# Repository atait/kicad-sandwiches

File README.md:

# KiSandwich
# KiSandwich

A KiCad plugin for designing **sandwich PCBs** — multiple boards bonded
together face-to-face into one device. Doing this lets you hide components
completely inside the stack, get 4-layer routing out of a pair of 2-layer
boards, and build truly zero-profile hardware (business cards, wallet-thin
gadgets, embedded speakers and microSD slots).

This construction technique is new and rarely used, so no design tools exist
for it — professional or otherwise. KiSandwich is an attempt to fill that gap:
you design one combined board in KiCad, and the plugin splits it into the
individual 2-layer boards you actually fabricate and bond.

## Concept

## Why would you do this

1. **Zero-profile design.** Build truly flat hardware — slip it in a wallet, embed it in a case, or hide it completely.
2. **Hide your components.** Recess and even hide parts into the board for things like backlit capacitive buttons.
3. **Get more routing layers.** Effectively get 4-layer routing out of a pair of 2-layer boards (or 6-layer out of three).
4. **Populate both sides cheaply.** Put components on both faces even if your pick-and-place only does one side.

This builds on [Oreo construction](https://hackaday.com/2019/01/18/oreo-construction-hiding-your-components-inside-the-pcb/),
which has more reasoning and a build example.
## Installation
### Install kigadgets
This is a wrapper for KiCAD's python SWIG. It is needed for version-independent action plugins. Follow instructions at [kigadgets](https://github.com/atait/kicad-python).

### Install kicad-sandwich action plugin
Clone this repository. Symlink the whole thing (`kicad-sandwiches`) into your kicad user plugins directory. This directory is located in ${KICAD_USER_DIR}/scripting/plugins, where ${KICAD_USER_DIR} depends on your operating system. You can find out where it is using the menu item "Tools > External Plugins > Reveal Plugin Folder". On macOS, you can avoid the terminal by right clicking the repo, making an "alias", and moving that alias to the plugins directory.

The next time you start pcbnew, you should see these icons in the menu bar.

If not, try going to Preferences>"action plugins" to search for them in the list and check the enable boxes.

## Examples
### Example files
The "examples" directory walks through a full design flow. The main design file is called "sandwich-example.kicad_pcb". It is designed as a 4-layer board with surface mount components on front and back. The image "pcbnew-snapshot.png" shows what the program *thinks* you are designing.

and here is what you are actually designing. Bottom board is green. Top board is red and transparent, and both ICs are recessed:

### Example footprints (tested and fabricated)
KiCAD footprints are found in kicad-sandwiches.pretty. Put them in a project library or a global library, and add that to your footprint paths to use them.

#### 2-board Arduino Nano
It is not quite zero profile because of the USBmicro but very close.

#### 3-board Arduino Nano
This is a 3-board sandwich with the Arduino Nano in the middle. It is completely hidden and zero profile. There is a hole so the reset button can be accessed.

#### Sandwich speaker
A zero-profile high-quality magnetic speaker (not a buzzer). It is almost exactly 5.2mm thick, so it fits with a 2mm midboard and 1.6mm outer boards. There is no room for screws, so it is glued in. Wire contacts are soldered to the midboard, so they are zero-profile too.

Tested with Digikey part: CLS0281MAE-L152

#### Hidden microSD card slot
A microSD card slot that is completely hidden and zero profile. It is accessed from the side of the sandwich.

## Designing
#### Actual layer meanings
The real thing will be stacked in the opposite order. F.Cu and B.Cu are used to represent the layers on the inside of the sandwich, while In1.Cu and In2.Cu represent what will become the outside of the sandwich. F and B will bond to one another with solder.

The reason for doing this is that blind vias make sense (except blind vias between In1 and In2). Components can be placed on F and B, but not In1 and In2. Most of the same DRC still applies, for example, a trace on F.Cu can pass over a buried via between B and In2.

**User.Eco1** makes cuts in the TOP board. Make sure cuts defined by Eco1 do not intersect footprints on Back. If it is a 2-board internal stack, put Eco1 openings around footprints on Front.

**User.Eco2** makes cuts in the LOW board. Make sure cuts defined by Eco2 do not intersect footprints on Front. If it is a 2-board internal stack, put Eco2 openings around footprints on Back.

**Margin *or* User.3** make cuts in the MID board if there is a 3-board stackup (i.e. 6 copper layers). In a 3-board stack, make sure there are slots in this layer for all footprints on front or back.

#### Running the scripts
Using the kisandwich plugin, this "board" is converted to two other files corresponding to the actual 2-layer boards: "kisandwich-out/sandwich-example-sandwich_\[LOW|TOP\].kicad_pcb". The plugin is activated with the  button, which gives a dialog with various options.

There are also entry points available to external python environments. These work on board files instead of the GUI's board.

#### Bonding pads
If you want a standard through via on one of your resulting boards, make this a *buried* via in the base design. A buried via between F.Cu/In1.Cu will get converted to a regular via on the LOW board. Buried vias between In1.Cu and In2.Cu make no sense! Those correspond to layers on the outside of the stackup.

kisandwich will interpret through vias as bonding points. It will tent them (covered by solder mask) on the outer sides, and de-tent them on the insides so that a big copper pad is exposed. When you get the PCBs, you put solder paste on these pads and reflow. Having a hole is extremely useful so you can stick in a soldering iron in case your reflow doesn't yield 100%.

Recommended bond pad parameters: Via diameter = 2 mm; Via hole = 1 mm

#### FreeCAD integration
In the same directory, all the boards are exported to VRML (.wrl) models.

**Todo: is this automated yet? KiCad 7 changed some VRML entry points**

**Todo: describe FreeCAD plugin installation here**

The models are assembled together in FreeCAD in the file "FreeCAD-out/stack-3dModel.FCStd". In FreeCAD, the lower board is translated down by one board thickness, and their appearances can be altered. Finally, a snapshot of the FreeCAD assembly is included in "FreeCAD-out/assembled-snapshot.png".

#### DRC
Both the source combined design and kisandwich outputs should roughly make sense as PCBs. The whole process of kisandwiches is designed to make both perspectives sensible.
The outputs must be valid 2-layer PCBs. The combined design should be a valid 6-layer or 4-layer PCB design, just with some new features and some other features verboten. This means DRC is a valid and highly useful tool.

The overall design should pass DRC, except for board outline violations. This will catch things like wires too close, and it won't hit non-errors like F.Cu crossing a B.Cu/In2.Cu buried via. It might have strange hits on edge aspects, which is what the individual-output board DRC is for.

All of the kisandwich-out boards should also pass DRC: clean. This will catch things like inclusion of tracks within edge cuts. KiCad's routing assistant does not know which Eco layers to avoid. That means (for a 3-board stackup) there are 4 DRCs to do: one for the combined design, and one for each of the three boards. They are meant to help you, so suck it up, iterate, and hunt down those errors.

#### Ctrl-Z
It finally works now. This was revolutionary. You can preview TOP, Ctrl-Z, preview LOW, Ctrl-Z without modifying anything or creating temporary files. It is recommended that you close and reopen the file after previewing the sandwiches *without saving*, just in case. As far as I know, Ctrl-Z works 100%, but just in case.

## Advanced features for 3-board stackups
See `kisandwich/three_board.py` for full information about modified layer mappings.

### 6-layer routing
As before, In1.Cu will map to B.Cu of the LOW board. Similarly, the lowest internal routing layer will map to F.Cu of the TOP board; however, that lowest layer is now In4.Cu instead of In2.Cu. Now, In2.Cu and In3.Cu will map to the MID board's F.Cu and B.Cu.

The vias get more complicated now. As before, a little buried via between F.Cu/In1.Cu will result in a normal through via on LOW. Likewise, buried B.Cu/In4.Cu -> through on TOP, and buried In2.Cu/In3.Cu -> through on MID.

A through via will get turned into through vias on all boards for bonding - make sure they use the recommended parameters above. kisandwich will take care of tenting.

What about buried vias In1.Cu/In2.Cu and In3.Cu/In4.Cu? These also get turned into bond pads. Make sure they use recommended diameter/drill parameters. The difference is that these bond pads are still buried, going only between LOW/MID or only between MID/HIGH.

### Footprints defining cuts
Any footprint whose *Value* field starts with "KISANDWICH-CUTTER" will have its graphic objects on Eco1, Eco2, Margin, User.3 interpreted as cuts, just as if they were drawn in the PCB file itself. This is very useful if you have some mechanical component stuck in the boards and need to move it around while keeping all cuts aligned. For example, a zero-profile screw point or an embedded speaker.

### Footprints on MID
Any footprint whose *Value* field starts with "KISANDWICH-MIDBOARD" will end up on the MID and removed from TOP and LOW. Front stays as Front, and Back as Back. I'm not sure when you would want to do this with an IC; maybe it is a sensor of some kind. Where this gets more useful is with modules with vector art that you want to expose through one of the Eco cuts.

### Drawing on MID
This requires a text editor. Open your .kicad_pcb file and add layers starting with "Mid." as shown below. The layer numbers don't matter because kigadgets will find them by name. Note, the exact format of this file might depend on version of kicad

```
(layers
  (0 "F.Cu" signal)
  (1 "In1.Cu" signal)
  ...
  (49 "F.Fab" user)
  (60 "Mid.F.SilkS" user)
  (61 "Mid.B.SilkS" user)
  (62 "Mid.F.Mask" user)
  (63 "Mid.B.Mask" user)
)
```

### Stencil creation
This does not work great for 2-board because both have components placed. With 3 boards, you want to use a stencil on both sides of MID, which likely does not have pre-placed physical components. There is a stencil option in the popup window, which is probably self explanatory for the most part. Even if you don't make a physical stencil, the stencil layout will point out places that bonds will go.

## Construction methodology
I have so far made 4x 2-board designs, and about 5x 3-board designs. I have mass produced about 150x copies of these designs in batches. Full documentation of that process with pictures is on the way... A quick summary will have to do for now.

### What you need
- Crocodile clamps. These apply a lot more force than alligator clamps
- Solder paste. Preferably a low-temperature eutetic alloy
- Remote oven thermometer. It is best to use its air probe, but I think a meat probe is fine
- Timer
- Cooling rack, or anything to which you can attach the probe
- Parchment paper
- Soldering iron with a fine (<1 mm), conical tip
- Continuity tester like the one on most multimeters

### Procedure for attaching 2 boards
No stencil here. Take your solder paste in a syringe, and put dabs directly on bond pads, one-by-one. Gently mate LOW with TOP, then use croc clamps to squeeze. The rest of the steps are same as below

### Procedure for attaching 3 boards w/ stencil
- Using the TOP stencil, apply paste to the MID board
- Gently put the MID board on top of the TOP board
- Using the LOW stencil, apply paste to the other side MID board, now facing up
- Gently put the LOW board on that fresh layer of paste
- Squeeze together using crocodile clamps, and make sure the alignment is good

### Procedure for reflow bonding
- Preheat your oven to ~400 F
- Get the little card that came with your solder paste that has optimal reflow profile. Put it next to your oven
- Arrange your boards with croc clamps on parchment paper on the cooling rack
- Attach the thermometer probe so that it is close to the PCBs but not touching anything solid
- Slide out an oven rack, and put the cooling rack (or whatever thing) on the oven rack
- Do not return the oven rack. Let it warm up a bit. 60 seconds tends to work.
- Slide in the oven rack. While watching temperature, let it get to the starting temp specified on the card
- While closely watching timer and comparing to the card, *partially* close and open the oven door to follow the profile
- For the "hit it" period, fully close the oven. Let it get *slightly* hotter for *slightly* longer than specified
- Fully open the oven. As it cools, slowly slide out the oven rack until you reach the card's end temperature
- Take the whole thing out and let it cool

### Procedure for rework
Yield is pretty good but less than 100%. You can use a continuity meter on the outside of the stackup to see what didn't connect. This does not work on buried bond pads, so you also have to rely on functional testing. LED not lighting up? It probably has something to do with the bond pad to that LED.

Jam the soldering iron with sharp conical tip into the hole of the disconnected bond pads. This will not damage good bonds, so you could just do this on every bond. If there was not enough solder paste, you sometimes have to cut off a few millimeters of solder wire, stick that in the hole, then bring in the soldering iron.

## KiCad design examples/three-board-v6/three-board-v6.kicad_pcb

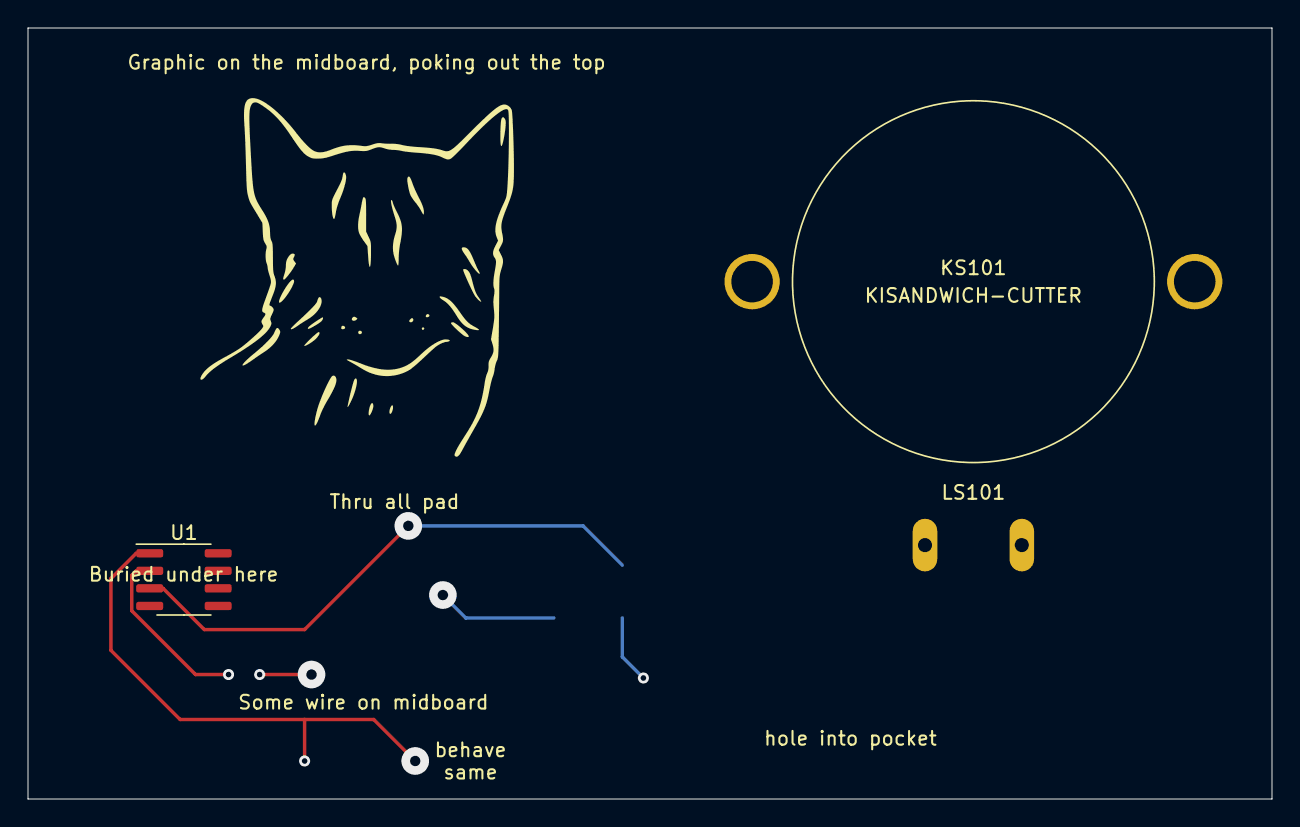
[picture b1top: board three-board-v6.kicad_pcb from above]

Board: 6 copper layers, 89.9 x 55.8 mm, 6 parts (1 on the bottom side), 2 nets.

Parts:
G1: KISANDWICH-MIDBOARD; cat_02
KS101: KISANDWICH-CUTTER; CUI-speaker-3layer-tight
LS101: KISANDWICH-MIDBOARD; Speaker_CUI_CLS0281MAE_embedded
U1, U2: LM555xM; SOIC-8_3.9x4.9mm_P1.27mm
svg2mod: KISANDWICH-CUTTER; light-hole

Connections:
unnamed: U1.2, U2.1
unnamed: U1.3, U2.5

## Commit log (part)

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2021-02-03 added bulk of code
2021-02-03 fixing paths
2021-02-03 file renames in sandwich
2021-02-03 debugged imports so it works again
2021-02-03 better one push scripting
2021-02-04 updated kisandwich gui
2021-02-04 added but disabled quick reload because there is no way to load from commands
2021-02-04 via processing fix
2021-02-05 implemented processing step options
2021-02-05 implemented bond pad options
2021-02-05 added example project
2021-02-05 added final 3d model
2021-02-05 snapshot from pcbnew
2021-02-05 put in the readme
2021-02-05 untrack freecad backup
2021-02-05 better 3d model using VRML and its snapshot
2021-02-05 fixed an unsupported font
2021-02-05 support python 2
2021-02-07 custom mapping layers
2021-02-09 relative path bug
2021-02-09 searching for pcbnew from scripting support to support CLI
2021-02-12 Zone layer mapping and remove other Eco's
2021-02-13 new GUI and inverse kind of sandwich
2021-02-15 options to bond using margin layer
2021-02-15 consolidated options handling
2021-02-18 drawings on copper
2021-03-02 option to remove outer side of bond pads. This looks better and technically enables more routing options, but DRC will not allow you to route there
2021-03-04 started on 3-board extension. Backwards compatibility: Use F.Paste instead of Margin for bond drawings
2021-03-04 started 3 board example
2021-03-04 further debugging. Modules working
2021-03-04 tracks working, and buried vias working
2021-03-04 vias and bond pads working. checked with inside and outside styles
2021-03-04 saved the outputs
2021-03-07 Special modules for cutting, meaning that the drawings from within the modules are exploded to cut layers
2021-03-07 Made 3D representations. Changed speaker to being placed on midboard. Checked heights
2021-03-07 Also processing copper that is in cutter modules
2021-04-30 settings bug
2021-05-01 Support for graphics on the middle board using special layers
2021-05-05 Auto stenciling
2021-05-05 adjusted stencil offset slightly
2021-05-07 Freecad import macro
2021-05-07 better file handling in macro
2021-05-07 Macro now handles VRML exported from kicad
2021-05-10 stencil fill GUI option
2021-05-10 Single side pads now get the net of the originating via
2021-05-10 Mid.F.Mask is actually a copper layer, so it wasn't getting caught by drawings processing'
2021-05-28 changed stencil fill factor default
2021-05-30 Putting stencil paste in the midboard
2021-06-23 changed default stencil opening ratio for bond pads. This is associated with AplusV4 (note the 4)
2021-07-13 Sometimes have to set radio defaults manually
2022-01-01 Use "is_through" semantics
2022-01-01 UI updates for v6: breaking
2022-01-01 Layer names for v6: breaking
2023-05-06 v7 deleting from an iterable
2023-05-06 Default options
2023-05-07 Layer and entry point adjustments
2023-05-07 Rely on kicad-python to find pcbnew
    tmp
2023-05-07 VRML attempt (not working in v6)
    tmp
2023-05-07 Try again on saving from GUI. Still can't prevent refresh
2023-05-07 Updated basic example to v6 standard directory format
2023-05-07 Three board pre-v6 example. It's a bit dicey. You should upgrade
2023-05-07 Fully updated v6/7 example of three boards
2023-05-07 New gitignores
2023-05-07 README including my process
2023-05-15 working multi-layer zones
2023-05-15 generic updates
2023-05-15 mousebite script, not working
2023-12-29 slight cut down on action plugin example
2023-12-30 working mousebite example
2023-12-31 artwork for the mouse
2023-12-31 GUI for mousebite
2023-12-31 Better looking GUI
2023-12-31 fillet: it is not working
2023-12-31 bugfix relative import
2024-01-06 Mousebite better
2024-01-08 retesting mousebiting
2024-01-08 fixup
2024-01-20 renamed mousebite example
2024-01-24 kigadgets 4.99 migration
2024-01-30 Rename kireload imports
2024-01-30 Get rid of relative imports. Might make python2 angry?
2024-01-30 Better function in mousebite
2024-01-30 Initial testing framework using lytests
2025-01-20 migrated examples to kigadgets
2025-01-20 Testing for sandwiches
2025-01-20 smarter importing
2025-01-20 kigadgets 5.0 syntaxes
2025-01-20 Version 8 layer names
2025-01-20 KISANDWICH CUTTER for speakers and stuff
2026-01-18 Minor style/import changes
2026-01-18 New kireload pattern
2026-01-18 Split tests by version
2026-01-18 Actual headless CLI entry point
2026-01-18 Versioning, license, and installation capabilities
2026-01-18 and ignore build files
